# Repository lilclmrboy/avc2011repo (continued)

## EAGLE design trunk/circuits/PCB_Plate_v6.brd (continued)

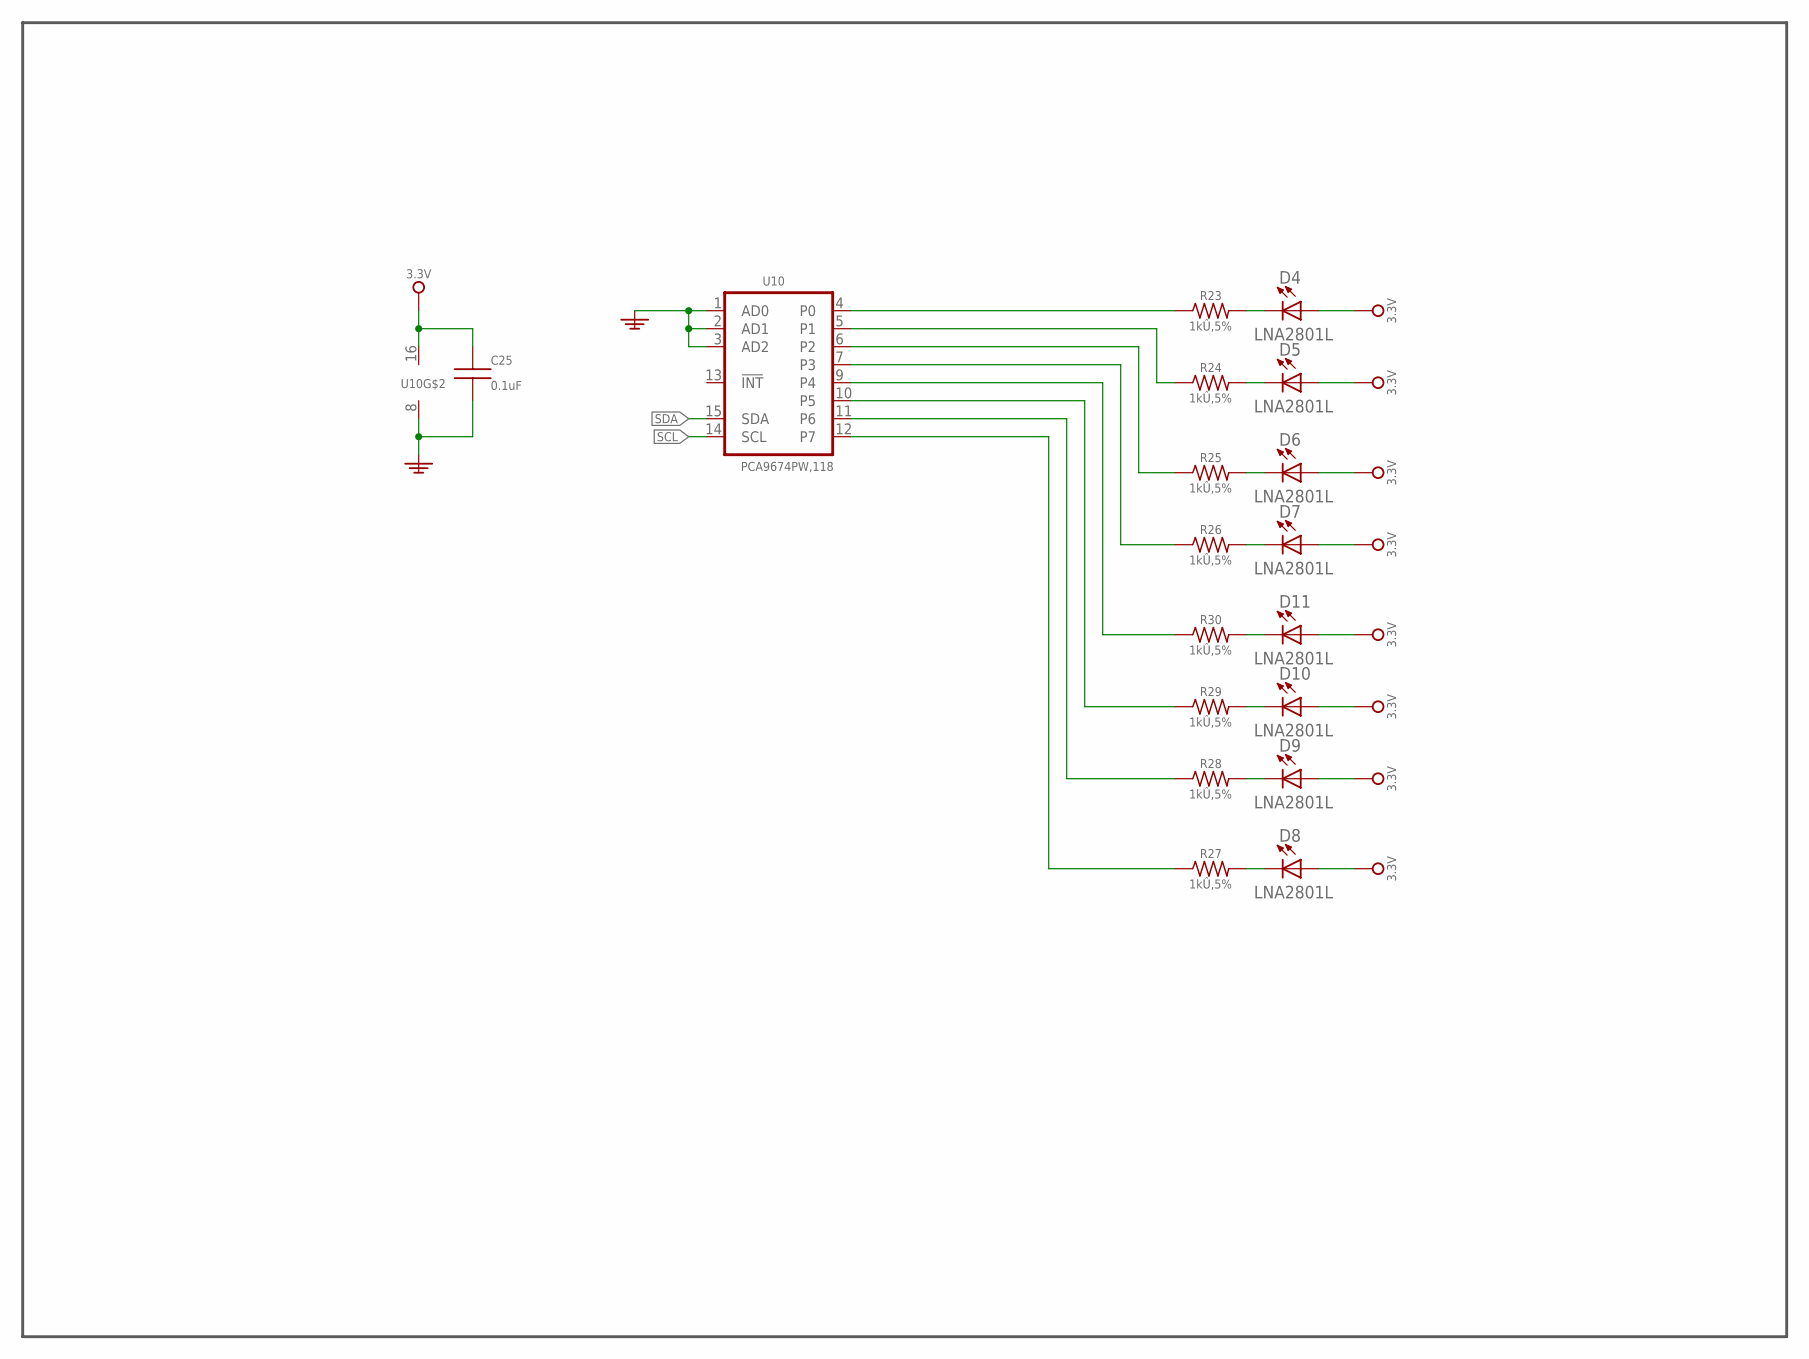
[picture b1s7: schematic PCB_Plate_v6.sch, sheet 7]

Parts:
C25: PCAPI00015; C0603
D4, D5, D6, D7, D8, D9, D10, D11: PDIOD00003; LT3LR1N02-001
R23, R24, R25, R26, R27, R28, R29, R30: PRESI00012; CFR-12
U10: I2C_DIO_EXPANDER; TSSOP16

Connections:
3V3: C25.1, D4.A, D5.A, D6.A, D7.A, D8.A, D9.A, D10.A, D11.A, U10.16 (VCC); also elsewhere on the board
GND: C25.2, U10.1 (AD0), U10.2 (AD1), U10.3 (AD2), U10.8 (GND); also elsewhere on the board
unnamed: D4.C, R23.P$2 (2)
unnamed: R23.P$1 (1), U10.4 (P0)
unnamed: D5.C, R24.P$2 (2)
unnamed: D6.C, R25.P$2 (2)
unnamed: D7.C, R26.P$2 (2)
unnamed: D11.C, R30.P$2 (2)
unnamed: D10.C, R29.P$2 (2)
unnamed: D9.C, R28.P$2 (2)
unnamed: D8.C, R27.P$2 (2)
unnamed: R24.P$1 (1), U10.5 (P1)
unnamed: R25.P$1 (1), U10.6 (P2)
unnamed: R26.P$1 (1), U10.7 (P3)
unnamed: R30.P$1 (1), U10.9 (P4)
unnamed: R29.P$1 (1), U10.10 (P5)
unnamed: R28.P$1 (1), U10.11 (P6)
unnamed: R27.P$1 (1), U10.12 (P7)
SCL: U10.14 (SCL); also elsewhere on the board
SDA: U10.15 (SDA); also elsewhere on the board

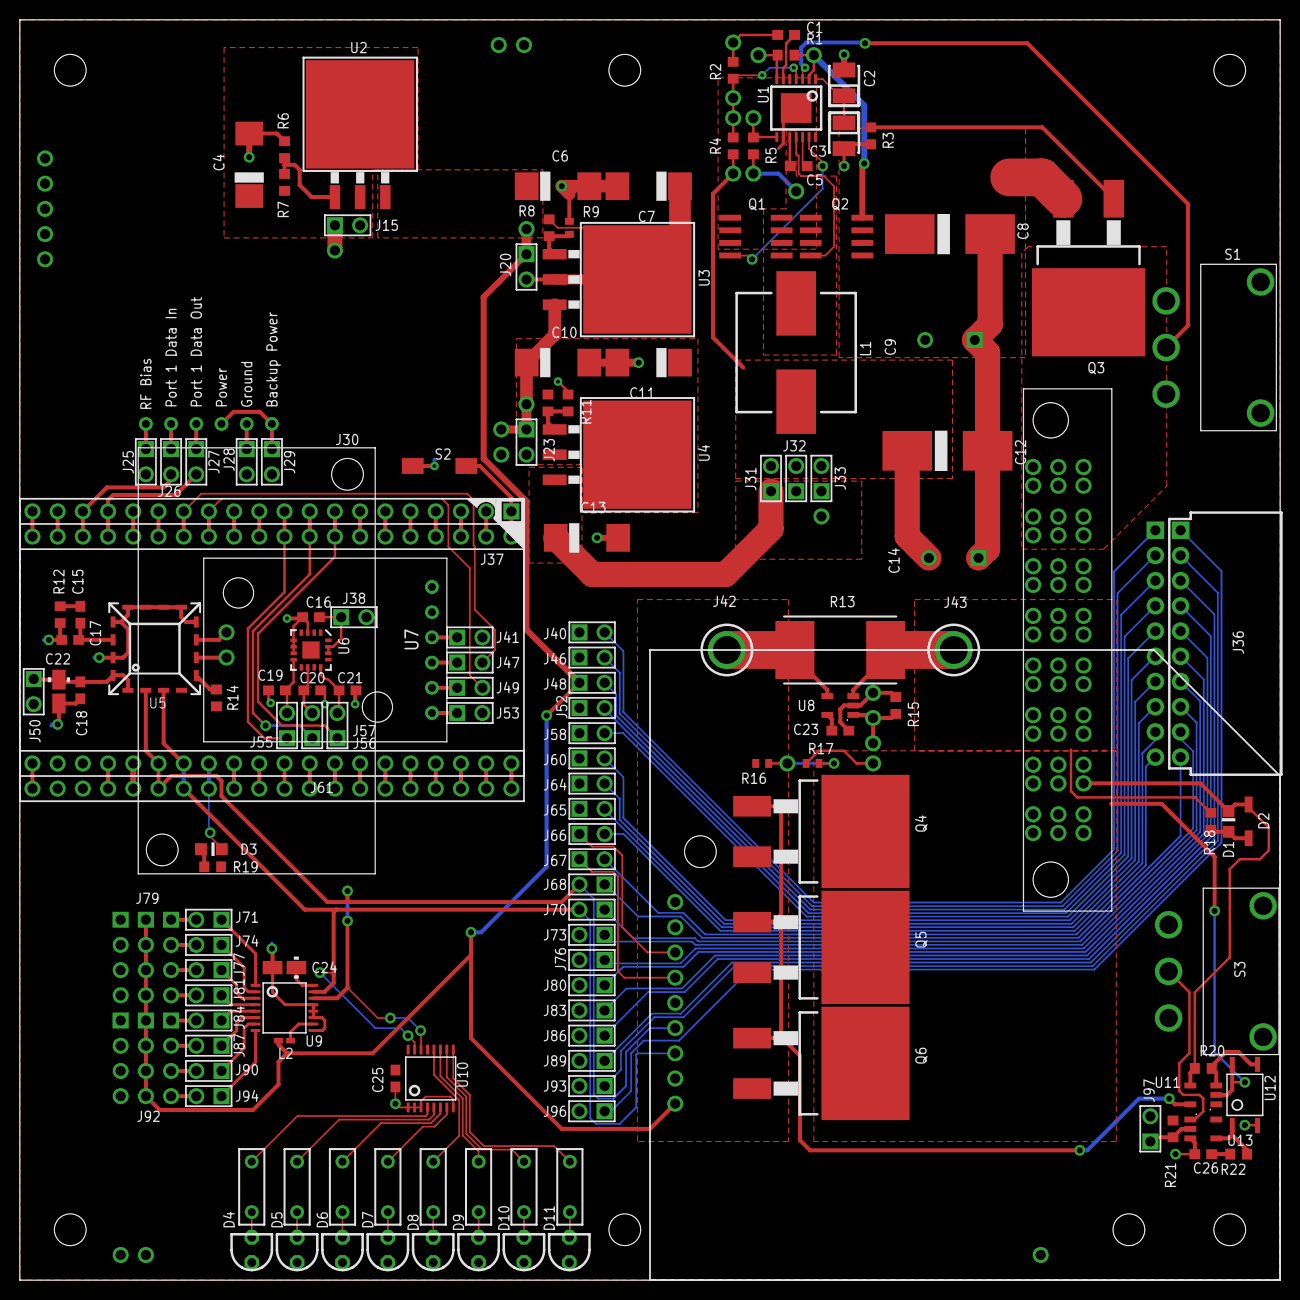
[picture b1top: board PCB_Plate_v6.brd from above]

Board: 2 copper layers, 127.0 x 127.0 mm, 198 parts (0 on the bottom side), 150 nets.

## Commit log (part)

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2011-03-16 broke the logger
2011-03-17 almost fixed logger, that I broke
2011-03-17 logger fixed, now planner is broken
2011-03-17 fixed app and planner for new logger
2011-03-19 Commented out sonar and ir polling threads to allow RC interaction to take over.
2011-03-21 updated RC control values
2011-03-22 More mucking with motion configuration parameters
2011-03-22 RC updates added deadband, divisor, and neutral variables
2011-03-23 removed polling from the location polling thread
2011-03-23 removed all enable bits
2011-03-23 logging GPS coordinates to GPX format
2011-03-23 moved rc enable to scratchpad locations and update motion thread
2011-03-25 Fixed motion settings after rewire, updated control settings, fixed debug string functions. It works.
2011-03-25 updated tarfile for linux to include moto app
2011-03-25 Tweaking sucks. And it's not done. Ugh
2011-03-30 Have a limping robot. No more dead FETs. Lot's of blown fuses.
2011-04-06 pwm frequency set to 2.441KHz
2011-04-10 Added testing ability with no GPS to try to return to same 0,0 starting point.
2011-04-10 checkGPS
2011-04-10 first round running against robot
2011-04-10 fixed typo in xml
2011-04-11 Added logging class to motion module. Also added RC over ride check
2011-04-11 Added debug log to motion setpoint action
2011-04-12 Added the ir repulsive sensor layer to the C++
2011-04-15 Added more sensors and tested the planner. It actually works. Next, put the ITX on it
2011-04-19 initial position updates
2011-04-19 Sonar sensor integration
2011-04-19 track to last waypoint
2011-04-20 Getting funky behavior with stems timing out. A holes
2011-04-21 Added user sounds
2011-04-21 compressed audio and added "thatsucked.wav"
2011-04-21 added southpark sounds
2011-04-21 Testing repulsive forces against the planner
2011-04-21 Deleted manual over ride section in motion module
2011-04-21 added check and reconnect function in controller
2011-04-21 Well. We need to sleep. It's been a good ride.
2011-04-21 Link down reflex should trigger manual over ride. When link is re-established, we allow autonomous control.
2011-04-21 Included updated GP2 reflexes tea file and tweaked makefile
2011-04-21 work in progress. Mostly driving with basic N/S map.
2011-04-22 Turned off the link down reflex
2011-04-22 Added in random chicken sounds
2011-04-22 More clucking sounds
2011-04-23 working in parkinglot
2011-04-23 added K-Filter
2011-04-23 logging track
2011-04-23 I'm Stupid
2011-08-10 Added a single braindump file for 2012 and makefile change
2011-08-10 Added some files to help work on the pcb plate.
2011-08-11 started a bit of schematic capture
2011-08-11 A small bit of power inputs for motor side of things.
2011-08-12 Added current sensing to motor power line
2011-08-22 Added some samtec parts and a library file
2011-08-22 Adding lots of cad model work.
2011-08-22 Added some missing cad files
2011-08-29 Added rough dimension drawing of pcb
2011-08-30 Started the board layout based on CAD model
2011-10-03 PCB work. Tying things up, added mount holes to board layout. Loads more to do
2011-10-04 More schematic capture. Assigned pin functionality on 20 pin header
2011-10-10 Changing main 12.0V regulator to simple switcher
2011-12-30 checking in switching regulator schematic capture
2012-01-06 checking in minor pcb schematic changes. starting accel and gyro integration
2012-01-07 Added generalized sensor interface
2012-01-09 added i2c a2d interface for a wider range of sensor inputs
2012-01-09 added note about what accel to use
2012-01-10 minor pcb tweeks
2012-01-11 Added working tea code for low level servo control of robot
2012-01-12 Checking in some routing on the pcb and added Devantech compass to the schematic
2012-01-13 Minor routing to some LDOs
2012-01-17 Mostly routed the switching regulator
2012-01-21 added accelerometer and routed it
2012-01-22 routed motor current measurement
2012-01-22 moved connectors to mid plane of circuit board. jumpers for 20 pin connector are now together
2012-01-23 Started routing from 20 pin connector to patchbay
2012-03-08 checking in a fully routed top plate. can one take any longer?
2012-03-12 checking in board. revision a ready to go
2012-03-14 updated part numbers
2012-04-14 checking in schematic changes
2012-04-14 checking in current acroname mac download
2012-04-17 checking in shell of GUI app code to test sub systems
2012-04-18 added stemdebug file
2012-04-18 checking in gui app changes with super controls
2012-04-18 checking in tarball with updated acroname mac sources
2012-04-18 added gp 2.0 module check in gui app
2012-04-18 removed stemdebug file
2012-04-22 working on getting motion module to, well, work
2012-04-22 cleaned up motion module sweep. tested full circle range
2012-04-26 refreshing for 2012
2012-04-27 rudimentary input receiver to servo output
2012-04-27 checking in working gp servo code for RC control.
2012-04-28 checking in motion module rework for 2012
2012-04-28 added updated linux acroname distro with drivers
2012-05-01 basic opencv camera example
2012-05-01 checking in start of C++ repulsive force interface
2012-05-01 Make the repulsive code compile now. Geez.
2012-05-01 added a logger class and for loop around the update the repulsive force class
2012-05-02 added tests to locModule, updated gpsQuality function
2012-05-02 added more configuration file settings to repulsive force class. each sensor looks to it's own setting file for details
2012-05-03 gp2d12 force distance normalization and repulisive force radius setting
2012-05-03 basic flow
2012-05-03 flow mesh
2012-05-03 checking in working scaled distance sharp sensor force class
2012-05-04 - add map.track (example track only) - improved logging in planner - plannerTest now compiles - repulsiveTest verified with sensors - add IR sensor configs - improved logging in repulsiveForces - fix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
2012-05-04 - restore config strings for planner and controller - make SparkPathLargeStep the default map - add maps folder - add acroSquare map for driving a square in front of acroSupplyCo - add north-south ma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
2012-05-04 Moved servo control into own function
2012-05-06 threaded the repulsive force class. fancy pants
2012-05-07 Simplified repulsive sensor sub classes, added long range sharp sensor class
2012-05-09 checking in some working tests with againts the repulsive class with the motion vector fast
2012-05-09 added a deadband to the tea for servo control
2012-05-10 added xcode project for the motion planner
2012-05-10 removed crud from xcode project
2012-05-12 Start work on updating locModule (not much progress)
2012-05-22 preparation for empirical sampling of turning rate.
2012-05-25 wrote code to get compass readings and covert to radians
2012-05-26 - add error check to getAccel in locModule - add gps
2012-05-29 - tab changes in controller.cpp - update GPS functions in locModule - add gps to posTest - add limits.h and unistd.h to planner.cpp - add PATH_MAX for ubuntu compiles
2012-05-30 moved avc2011 files to avc
2012-05-30 cleaning up tea files
2012-05-30 more cleanup
2012-05-30 added max turn angle and cubic line fitting params
2012-05-31 getting loc module in shape
2012-06-05 - slow down main loop for test logging clarity - enable GPS in locModule - fix? dx, dy calc in locModule - add logging in planner
2012-06-05 - add gyro - add L3G4200D gyro
2012-06-06 We beat up the code pretty hard. Cleaned up a lot of code. Still not chasing the goal yet
2012-06-07 - fix scratch pad reading/writing confusions - fix lat/long mix in locModule - change to distance instead of velocity calcs to prevent rounding craziness - use #def for meter_per_tick in locMod insta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
2012-06-07 reworked main controller loop... probably broke stuff
2012-06-07 dude
2012-06-07 dude dude
2012-06-07 - add logger member to avcCompass - move compass to class - change heading to be in degrees (with rad option) - add CMPS10 to compass - remove L3G04200D and LSM303DLM headers - update makefile to sup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
2012-06-08 - update chicken.config for testing - add test for CMPS10 - add factory cal reset for CMPS10 - fix main controller loop timer - enable compass in locModule - disable first GPS fix for testing - disab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
2012-06-09 checking in v120530 download for acroname sources
2012-06-09 add input voltage measurement and configuration input settings
2012-06-09 - add CMPS10.cpp - add LSM303DLM accel and heading - fix all sorts of IIC craziness on LSM303DLM
2012-06-09 checking in test system with a fancy new compass and voltage monitoring
2012-06-09 adding death metal rooster sound
2012-06-10 - add loop delay and mapfile to chicken.config - move PlaySound to avc.h - remove voltage sound warning - switch to LSM303DLM compass - minor motionModule changes - flip y motivation from planner to 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
2012-06-10 - move ADXL335 accelerometer to the accelerometer class - change getAccelerometerReadings to return floats - more compass cleanup
2012-06-10 - add directions to map waypoints
2012-06-10 added TinyGPS NEMA sentence parsing app, fixed snow leopard xcode project
2012-06-10 added singleton gps class will need to fill in init, run, and get position methods.
2012-06-10 - change max_turnangle to smooth out steering - pass in throttle to locModule so we don't have to read it from the spad - remove locModule fRot and steer angle reading - add moving average to steerAn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
2012-06-12 - add pos/heading/target logger to controller - fix planner accessor functions for logger
2012-06-12 working gpsTest in makefile for new gps unit.
2012-06-13 Updated ADXL335 accel to return m/sec^2 values and do running avg if wanted. Fixed uninitialized variable warning in lcoModule
2012-06-13 - add accelerometer thread class - add hdop accessor to gps - add gps to locModule - fix build
2012-06-13 - add accelerometer thread to locModule - add unit test for accelerometer thread
2012-06-14 fixed 1 element arrays
2012-06-14 - add LSM303DLM.h - remove servo based +/- in locModule - correct ticks per meter with new encoder
2012-06-14 Updated error functionality in gps
2012-06-14 attempt at changing how we poll for encoder readings
2012-06-14 Fixed compiling warning cause I suck
2012-06-14 added GPS unit to location module. Currently within aUSE_GPS define which is defined in the makefile but commented out.
2012-06-15 Updated encoder tick rate after changing to a 4 quad disc
2012-06-15 how do you screw up comments? geez...
2012-06-15 Threaded the damn gyro class. Did some stats on the accel too
2012-06-15 - enable EKF
2012-06-15 added system call to turn sound card all the way up. not tested
2012-06-15 - check in from late night work 2012Jun15 - update meters per tick for new encoder wheel - update locPlan logging to include a call to the compass - fix gps init in locModule - remove accel thread in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
2012-06-16 - change max steer angle to 45 - change donut sizing - fix volume setting - fix locModule compile under optimization - fix motModule delta calc - fix planner for last point in map
2012-06-16 Fucking fixed all Justin's code. It goes to 11.
2012-06-16 split GPS config items out into separate settings file so we can run two aRelays
2012-06-16 added boolean to enable repulsive forces, and fixed the thread starting issues
2012-06-16 added startup linux script to cluck like crazy
2012-06-16 - update chicken.config - update sparkFunLargeStep - enable repulsion by default (dumb config files and setting bools) - flip gps error logic (untested) - enable and tweak declination correction - tu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
2012-06-16 - first run map - repulse disabled - wider turning
2012-06-17 - not tested in the field, but final code for 2012 - added repulse with long range (hack) - modified map (was tested, for first turn) - fix y-sign in planner adding of repulse and goal
2012-06-29 added a copy of the live version of sparkfun band song for the headless chicken
